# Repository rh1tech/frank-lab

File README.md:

# FRANK Lab

Official page: **[frank.rh1.tech](https://frank.rh1.tech/)** — hub for all FRANK boards and firmware.

Experimental and work-in-progress boards for the [FRANK](https://github.com/rh1tech/frank) hardware emulation platform.

**WARNING: These boards are untested and unreleased. Do NOT order PCBs from this repository.** They may contain errors, incomplete routing, or unverified component footprints. Use at your own risk.

For production-ready boards, see the main [frank](https://github.com/rh1tech/frank) repository.

## Boards in this repository

| Board | Status |
|-------|--------|
| `frank_air` | Work in progress |
| `frank_core2` | Work in progress — pulled back from the released set |
| `frank_pga` | Work in progress — single PGA2350, megafrank M2 pinout, composite + PS/2, 2-layer, hand-solderable |
| `frank_pga2` | 1.00 ready for fab, untested — dual PGA2350 (Core2 link), 2-layer, hand-solderable |
| `dino_z80` | Work in progress — pulled back from the released set |
| `xt8086_beta` | Work in progress — pulled back from the released set |
| `frank_next_proto` | Prototype — superseded by FRANK Next, released |

## Released from this repository

These boards have graduated to [rh1tech/frank](https://github.com/rh1tech/frank) and are no
longer maintained here:

| Was | Now |
|-----|-----|
| `frank_next` | [`hardware/frank_next`](https://github.com/rh1tech/frank/tree/master/hardware/frank_next) — the flagship |
| `frank_core2_proto` | [`hardware/frank_core2_proto`](https://github.com/rh1tech/frank/tree/master/hardware/frank_core2_proto) — published as a prototype |
| `frank_core2u` | [`hardware/frank_core2u`](https://github.com/rh1tech/frank/tree/master/hardware/frank_core2u) |
| `oldskoolfrank` | [`hardware/oldskool`](https://github.com/rh1tech/frank/tree/master/hardware/oldskool) |

Each carries its KiCad project, gerbers, fabrication docs, 3D-printable case and an assembly
guide in English and Russian. Board pages with full specifications are on
[frank.rh1.tech](https://frank.rh1.tech/hardware).

## Author

Mikhail Matveev — <xtreme@rh1.tech> — [rh1.tech](https://rh1.tech)

## License

© 2026 Mikhail Matveev, <xtreme@rh1.tech>

GPL v3. See [LICENSE](./LICENSE).

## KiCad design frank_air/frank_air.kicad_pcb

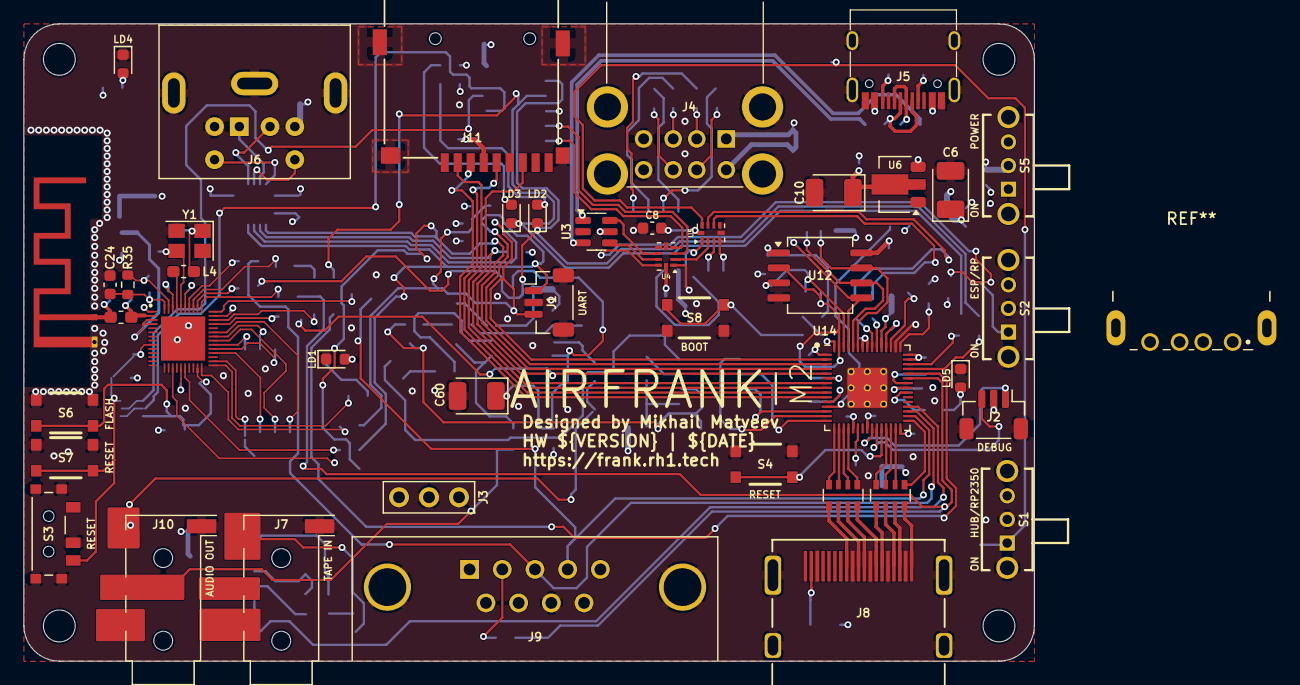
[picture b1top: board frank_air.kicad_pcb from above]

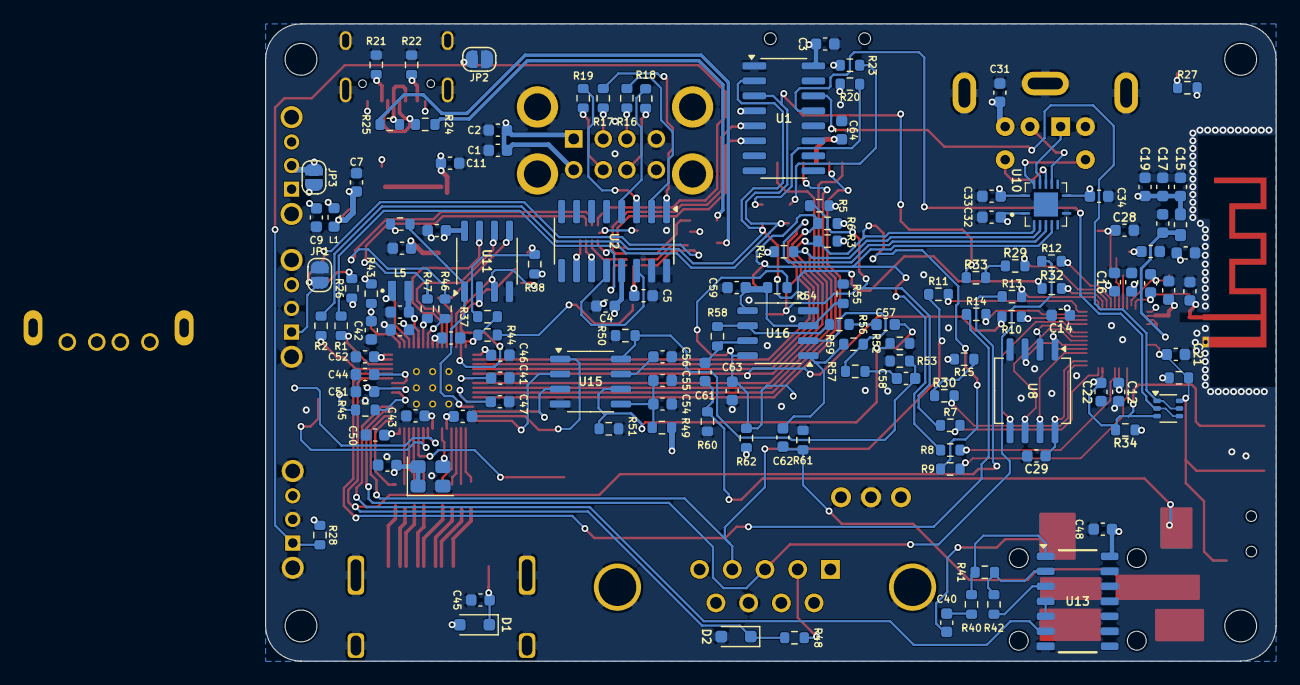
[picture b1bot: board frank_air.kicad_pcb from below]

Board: 4 copper layers, 85.6 x 54.0 mm, 183 parts (136 on the bottom side), 150 nets.

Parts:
AE1: Antenna_Shield; Antenna_2.4GHz
C1, C2, C54, C56, C57, C58, C59, C61, C62: 10u; C_0603_1608Metric
C3, C5, C7, C8, C9, C11, C31, C32, C33, C34, C35, C36, C37, C40, C41, C44, C45, C46, C47, C48, C49, C50, C51, C52, C53, C55, C63, C64: 100n; C_0603_1608Metric
C4, C38, C39, C42, C43: 4.7u; C_0603_1608Metric
C6, C10: 22u; CP_Tantalum_3528-12
C12, C19: 1u; C_0603_1608Metric_HandSolder
C13, C15, C16, C18, C20, C29: 100n; C_0603_1608Metric_HandSolder
C14: 100p; C_0603_1608Metric_HandSolder
C17: 10u; C_0603_1608Metric_HandSolder
C21, C22: 1n; C_0603_1608Metric_HandSolder
C23: 1.5pF; C_0603_1608Metric_HandSolder
C24: 10n; C_0603_1608Metric_HandSolder
C25: 2.4pF; C_0603_1608Metric_HandSolder
C26: 3.3n; C_0603_1608Metric_HandSolder
C27, C28: 12p; C_0603_1608Metric_HandSolder
C60: 10u; CP_Tantalum_3528-12
D1: 1N5819WS; D_SOD-323
D2: 3V3; D_SOD-323
H1, H2, H3, H4: Hole 2.7mm; MountingHole_2.7mm
J1: UART; JST_SH_1x03_P1.00mm_Vertical
J2: DEBUG; JST_SH_1x03_P1.00mm_Vertical
J3: PWR; PinHeader_1x03_P2.54mm
J4: SS-52100-004; USB_A_Stacked
J5: USB4215-03-A; USB_C_Receptacle
J6: MDC-036; MiniDIN_6pin_Female
J7: PJ-320D; AudioJack_3.5mm_PJ320D_TapeIn
J8: HDMI-001 19PCBTP; HDMI_Female
J9: GP2; DSUB-9_Male_TopMount
J10: PJ-320D; AudioJack_3.5mm_PJ320D_AudioOut
J11: 104031-0811; MicroSD_SMD_Long
JP1: SW1 Dbg; SolderJumper-2_P1.3mm_Open_RoundedPad1.0x1.5mm
JP2: SW2 Dbg; SolderJumper-2_P1.3mm_Open_RoundedPad1.0x1.5mm
JP3: VBUS_IN Dbg; SolderJumper-2_P1.3mm_Open_RoundedPad1.0x1.5mm
L1: 330R; L_0603_1608Metric
L2: 2nH; Inductor_0603_1608Metric_HandSolder
L3: 2.7nH/0R; Inductor_0603_1608Metric_HandSolder
L4: 24nH/0R; Inductor_0603_1608Metric_HandSolder
L5: 3.3u; L_pol_2016
LD1, LD5: Blue; LED_0603_1608Metric
LD2, LD3: Orange; LED_0603_1608Metric
LD4: Green; LED_0603_1608Metric
Q1: UMH3N; SOT-363
R1, R2, R7, R8, R9, R10, R11, R12, R13, R14, R27, R44, R45, R48: 1K; R_0603_1608Metric
R3, R4, R5, R6, R26, R28, R38, R39, R52, R53, R54, R55, R56, R57: 10K; R_0603_1608Metric
R15, R50, R51: 470R; R_0603_1608Metric
R16, R17, R18, R19, R24, R25: 22R; R_0603_1608Metric
R20, R23: 1.5K; R_0603_1608Metric
R21, R22: 5.1K; R_0603_1608Metric
R29: 499R; R_0603_1608Metric_HandSolder
R30: 0R; R_0603_1608Metric_HandSolder
R31, R34: 10K; R_0603_1608Metric_HandSolder
R32, R33: 330R; R_0603_1608Metric_HandSolder
R35: 20K; R_0603_1608Metric_HandSolder
R37: 0R; R_0603_1608Metric
R40: 4.7K; R_0603_1608Metric
R41, R42: 100K; R_0603_1608Metric
R43: 33R; R_0603_1608Metric
R46, R47: 27R; R_0603_1608Metric
R49, R62: 100R; R_0603_1608Metric
R58, R59: 47K; R_0603_1608Metric
R60, R61: 20K; R_0603_1608Metric
RN1, RN2: 270R; R_Array_4x0603
S1, S2: SK12D07VG3NS
S3: MSK12C02; Switch_Slide_MSK12C02
S4, S8: RP Reset; KMR_2
S5: SK12D07VG3NS; SK12D07VG3NS_PWR
S6: ESP Flash; KMR_2
S7: ESP Boot; KMR_2
U1: CH340C; SOP-16
U2: MW7211A; SOP-16
U3: USBLC6-2SC6; SOT-23-6
U4, U5: TS3USB221RSER; UQFN-10
U6: AMS1117-3.3; SOT-89-3
U7: ESP32-D0WD-V3; QFN35P500X500X90-49N-D
U8: W25Q32JVSIQ; SOIC-8
U10: TXS0104ERGYR; RGY_S-PVQFN-N14
U11: ESP-PSRAM32; SO-8
U12: W25Q128JVS; SOIC-8
U13: CD4069UBM; SOIC127P600X175-14N
U14: RP2350; QFN-60_RP2350A
U15: TDA1387T; SO-8
U16: LM358; SO-8
Y1: 40MHz; Crystal_SMD_3225-4Pin_3.2x2.5mm
Y2: ASE-12MHz; Oscillator_SMD_4Pin_3.2x2.5mm

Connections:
+1V1: C39.1, C41.1, C43.1, C44.1, L5.1, U14.6 (DVDD), U14.23 (DVDD), U14.39 (DVDD), U14.50 (VREG_FB)
+3.3VP: C13.1, L2.2, U7.3 (VDD3P3_1), U7.4 (VDD3P3_2)
+3V3: C3.1, C5.2, C8.2, C10.1, C11.2, C12.1, C14.1, C15.1, C16.1, C17.1, C18.1, C19.1, C20.1, C32.1, C34.1, C35.1, C36.1, C37.1, C38.1, C46.1, C47.1, C48.1, C49.1, C50.1, C51.1, C52.1, C53.1, C64.2, J3.1, J11.4 (VDD), L2.1, R3.2, R4.2, R5.2, R6.2, R20.2, R23.1, R26.1, R27.2, R28.1, R31.2, R34.2, R38.1, R39.2, R43.1, U1.4 (3V), U1.16 (VCC), U4.10 (VCC), U5.10 (VCC), U6.2 (VO), U7.1 (VDDA_1), U7.19 (VDD3P3_RTC), U7.37 (VDD3P3_CPU), U7.43 (VDDA_2), U7.46 (VDDA_3), U10.1 (VCCA), U10.8 (OE), U11.8 (VCC), U12.8 (VCC), U13.14 (VDD), U14.1 (IOVDD), U14.11 (IOVDD), U14.20 (IOVDD), U14.30 (IOVDD), U14.38 (IOVDD), U14.44 (ADC_AVDD), U14.45 (IOVDD), U14.49 (VREG_VIN), U14.53 (USB_OTP_VDD), U14.54 (QSPI_IOVDD), Y2.1 (EN), Y2.4 (Vdd)
/Audio/AMP_OUTL: C61.2, J10.T, R60.2
/Audio/AMP_OUTR: C62.2, J10.R, R61.2
/Audio/TDA_L: C57.1, R51.2, R52.1, U15.6 (A_LEFT)
/Audio/TDA_R: C58.1, R50.1, R53.1, U15.8 (A_RIGHT)
/D+: R46.1, U5.8 (D+)
/D-: R47.1, U5.7 (D-)
/ESP32/ANT: AE1.1 (A), C25.1, L3.1
/ESP32/CAP1: C24.1, C26.1, R35.2, U7.48 (CAP1)
/ESP32/CAP2: C26.2, R35.1, U7.47 (CAP2)
/ESP32/DTR: Q1.2 (B1), Q1.4 (E2), U1.13 (DTR)
/ESP32/GPIO4: R7.2, U7.24 (GPIO4)
/ESP32/GPIO13: R8.2, U7.20 (MTCK)
/ESP32/GPIO14: R9.2, U7.17 (MTMS)
/ESP32/GPIO16: R15.1, R30.2
/ESP32/GPIO18: R10.2, U7.35 (GPIO18)
/ESP32/GPIO19: R11.2, U7.38 (GPIO19)
/ESP32/GPIO21: R12.2, U7.42 (GPIO21)
/ESP32/GPIO22: R13.2, U7.39 (GPIO22)
/ESP32/GPIO23: R14.2, U7.36 (GPIO23)
/ESP32/LNA_IN: C23.1, L3.2, U7.2 (LNA_IN)
/ESP32/RTS: Q1.1 (E1), Q1.5 (B2), U1.14 (RTS)
/ESP32/SCK/CLK: U7.31 (SD_CLK), U8.6 (CLK)
/ESP32/SCS/CMD: U7.30 (SD_CMD), U8.1 (~CS)
/ESP32/SDI/SD1: U7.33 (SD_DATA_1), U8.5 (DI(IO0))
/ESP32/SDO/SD0: U7.32 (SD_DATA_0), U8.2 (DO(IO1))
/ESP32/SHD/SD2: U7.28 (SD_DATA_2), U8.7 (IO3)
/ESP32/SWP/SD3: U7.29 (SD_DATA_3), U8.3 (IO2)
/ESP32/U0RXD: R32.2, U7.40 (U0RXD)
/ESP32/U0TXD: R29.2, R33.2
/ESP32/VDD_SDIO: C29.1, U7.26 (VDD_SDIO), U8.8 (VCC)
/ESP32/XTAL_N: C27.1, U7.44 (XTAL_N), Y1.3
/ESP32/XTAL_P: L4.1, U7.45 (XTAL_P)
/ESP Buttons/ESP_FLASH: C22.1, Q1.3 (C2), R34.1, S6.2, S6.4, U7.23 (GPIO0)
/ESP Buttons/ESP_RESET: C21.1, Q1.6 (C1), R31.1, S3.3, S7.2, S7.4, U7.9 (CHIP_PU)
/GPIO0: J1.1, R5.1, R7.1, U10.4 (A3), U14.2 (GPIO0)
/GPIO1: J1.3, R6.1, R8.1, U10.5 (A4), U14.3 (GPIO1)
/GPIO2: R3.1, R9.1, U10.2 (A1), U14.4 (GPIO2)
/GPIO3: R4.1, R10.1, U10.3 (A2), U14.5 (GPIO3)
/GPIO4: J11.7 (DAT0), U14.7 (GPIO4)
/GPIO5: J11.2 (DAT3/CD), U14.8 (GPIO5)
/GPIO6: J11.5 (CLK), U14.9 (GPIO6)
/GPIO7: J11.3 (CMD), U14.10 (GPIO7)
/GPIO9: U14.13 (GPIO9), U15.3 (DATA)
/GPIO10: U14.14 (GPIO10), U15.1 (SCLK)
/GPIO11: U14.15 (GPIO11), U15.2 (LRCK)
/GPIO12: RN1.4 (R4.1), U14.16 (GPIO12)
/GPIO13: RN1.3 (R3.1), U14.17 (GPIO13)
/GPIO14: RN1.2 (R2.1), U14.18 (GPIO14)
/GPIO15: RN1.1 (R1.1), U14.19 (GPIO15)
/GPIO16: RN2.4 (R4.1), U14.27 (GPIO16)
/GPIO17: RN2.3 (R3.1), U14.28 (GPIO17)
/GPIO18: RN2.2 (R2.1), U14.29 (GPIO18)
/GPIO19: RN2.1 (R1.1), U14.31 (GPIO19)
/GPIO20: J9.4, R11.1, U14.32 (GPIO20)
/GPIO21: J9.3, R12.1, U14.33 (GPIO21)
/GPIO22: U13.6 (I=*C), U14.34 (GPIO22)
/GPIO26: D2.1 (K), R13.1, R48.1, U14.40 (GPIO26_ADC0)
/GPIO27: R14.1, U14.41 (GPIO27_ADC1)
/GPIO28: LD2.1 (K), R2.1, R32.1, U1.2 (TxD)
/GPIO29: LD3.1 (K), R1.1, R33.1, U1.3 (RxD)
/PS2/KB_CLK_5V: J6.5, U10.13 (B1)
/PS2/KB_DATA_5V: J6.1, U10.12 (B2)
/PS2/MS_CLK_5V: J6.6, U10.11 (B3)
/PS2/MS_DATA_5V: J6.2, U10.10 (B4)
/Power/SW1: JP1.2 (B), R26.2, S2.1, U4.9 (S)
/Power/SW2: JP2.2 (B), R28.2, S1.1, U5.9 (S)
/Power/TC_D+: U3.4 (I/O2), U4.8 (D+)
/Power/TC_D-: U3.6 (I/O1), U4.7 (D-)
/Power/UH_D+: U2.11 (DPU), U5.3 (2D+)
/Power/UH_D-: U2.10 (DMU), U5.4 (2D-)
/Power/US_D1+: R16.1, U2.2 (DP0)
/Power/US_D1-: R17.1, U2.1 (DM0)
/Power/US_D2+: R18.1, U2.4 (DP1)
/Power/US_D2-: R19.1, U2.3 (DM1)
/Power/UT_D+: U1.5 (D+), U4.3 (2D+)
/Power/UT_D-: U1.6 (D-), U4.4 (2D-)
/Power/VBUS_IN: J5.2 (VBUS), J5.11 (VBUS), JP3.1 (A), S5.2
/RP2350A/FLASH_SS: R37.2, R38.2, U12.1 (~CS)
/RP2350A/GPIO8: R39.1, U11.1 (~CE), U14.12 (GPIO8)
/RP2350A/GPIO28: R2.2, U14.42 (GPIO28_ADC2)
/RP2350A/GPIO29: R1.2, U14.43 (GPIO29_ADC3)
/RP2350A/QSPI_SCLK: U11.6 (SCLK), U12.6 (CLK), U14.56 (QSPI_SCLK)
/RP2350A/QSPI_SD0: U11.5 (SI/SIO), U12.5 (DI(IO0)), U14.57 (QSPI_SD0)
/RP2350A/QSPI_SD1: U11.2 (SO/SIO), U12.2 (DO(IO1)), U14.59 (QSPI_SD1)
/RP2350A/QSPI_SD2: U11.3 (SIO2), U12.3 (IO2), U14.58 (QSPI_SD2)
/RP2350A/QSPI_SD3: U11.7 (SIO3), U12.7 (IO3), U14.55 (QSPI_SD3)
/RP2350A/QSPI_SS: R37.1, R44.1, U14.60 (QSPI_SS)
/RP2350A/SWCLK: J2.3, U14.24 (SWCLK)
/RP2350A/SWD: J2.1, U14.25 (SWD)
/RP2350A/VREG_AVDD: C42.1, R43.2, U14.46 (VREG_AVDD)
/RP2350A/VREG_LX: L5.2, U14.48 (VREG_LX)
/RP2350A/XIN: U14.21 (XIN), Y2.3 (OUT)
/RP2350A/~USB_BOOT: R44.2, S8.2, S8.4
/RUN: S4.2, S4.4, U14.26 (RUN)
/Tape In/TAPE: C40.2, J7.T
GND: AE1.2 (Shield), C1.2, C2.2, C3.2, C4.2, C5.1, C6.2, C7.1, C8.1, C9.2, C10.2, C11.1, C12.2, C13.2, C14.2, C15.2, C16.2, C17.2, C18.2, C19.2, C20.2, C21.2, C22.2, C23.2, C24.2, C25.2, C27.2, C28.2, C29.2, C31.2, C32.2, C33.2, C34.2, C35.2, C36.2, C37.2, C38.2, C39.2, C41.2, C42.2, C43.2, C44.2, C45.2, C46.2, C47.2, C48.2, C49.2, C50.2, C51.2, C52.2, C53.2, C54.2, C55.2, C56.2, C59.1, C60.2, C63.1, C64.1, D2.2 (A), J1.2, J2.2, J3.2, J4.4 (GND1), J4.8 (GND2), J4.SH (Shield), J5.1 (GND), J5.12 (GND), J5.13 (SHIELD), J6.3, J7.S, J8.2 (G_D2), J8.5 (G_D1), J8.8 (G_D0), J8.11 (G_CLK), J8.17 (G_DDC/CEC), J8.20 (SHIELD1), J8.21 (SHIELD2), J8.22 (SHIELD3), J8.23 (SHIELD4), J9.8, J10.S, J11.6 (VSS), J11.SH (SHIELD), JP1.1 (A), JP2.1 (A), LD1.1 (K), LD4.1 (K), LD5.1 (K), R21.1, R22.1, R50.2, R51.1, R52.2, R53.2, R55.1, R60.1, R61.1, S1.2, S2.2, S3.2, S4.1, S4.3, S6.1, S6.3, S7.1, S7.3, S8.1, S8.3, U1.1 (GND), U2.15 (GND), U2.16 (GND), U3.2 (GND), U4.5 (GND), U4.6 (~OE), U5.5 (GND), U5.6 (~OE), U6.1 (GND), U7.49 (GND), U8.4 (GND), U10.7 (GND), U10.15 (THERMAL_PAD), U11.4 (VSS), U12.4 (GND), U13.7 (VSS), U13.9 (D14), U13.11 (E), U13.13 (F), U14.47 (VREG_PGND), U14.61 (GND), U15.4 (AGND), U16.4 (V-), Y1.2, Y1.4, Y2.2 (GND)
GPIO25: R45.2, U14.37 (GPIO25)
unnamed: C28.1, L4.2, Y1.1
unnamed: C40.1, R40.2
unnamed: C57.2, R56.2
unnamed: C58.2, R57.2
unnamed: C61.1, R58.1, U16.7
unnamed: C62.1, R59.1, U16.1
unnamed: C45.1, D1.1 (K), J8.18 (+5V)
unnamed: J4.3 (D1+), R16.2
unnamed: J4.2 (D1-), R17.2
unnamed: J4.7 (D2+), R18.2
unnamed: J4.6 (D2-), R19.2
unnamed: J5.4 (CC1), R21.2
unnamed: J5.10 (CC2), R22.2
unnamed: J5.5 (DN2), J5.7 (DN1), R24.2
unnamed: J5.6 (DP1), J5.8 (DP2), R25.2
unnamed: J8.12 (CLKN), RN1.5 (R4.2)
unnamed: J8.10 (CLKP), RN1.6 (R3.2)
unnamed: J8.9 (D0N), RN1.7 (R2.2)
unnamed: J8.7 (D0P), RN1.8 (R1.2)
unnamed: J8.6 (D1N), RN2.5 (R4.2)
unnamed: J8.4 (D1P), RN2.6 (R3.2)
unnamed: J8.3 (D2N), RN2.7 (R2.2)
unnamed: J8.1 (D2P), RN2.8 (R1.2)
unnamed: J9.2, R48.2
unnamed: C9.1, JP3.2 (B), L1.2, S5.1
unnamed: LD1.2 (A), R15.2
unnamed: LD2.2 (A), R20.1
unnamed: LD3.2 (A), R23.2
unnamed: LD4.2 (A), R27.1
unnamed: LD5.2 (A), R45.1
unnamed: R24.1, U3.1 (I/O1)
unnamed: R25.1, U3.3 (I/O2)
unnamed: U2.12 (VD33), U2.14 (VD3)
unnamed: U4.1 (1D+), U5.1 (1D+)
unnamed: U4.2 (1D-), U5.2 (1D-)
unnamed: R30.1, U7.25 (GPIO16)
unnamed: R29.1, U7.41 (U0TXD)
unnamed: R40.1, R41.2, U13.1 (A)
unnamed: R42.1, U13.3 (B)
unnamed: U13.4 (H=*B), U13.5 (C)
unnamed: R41.1, R42.2, U13.2 (G-*A)
unnamed: R47.2, U14.51 (USB_DM)
unnamed: R46.2, U14.52 (USB_DP)
unnamed: C56.1, U15.7 (FLT)
unnamed: C54.1, C55.1, R49.1, U15.5 (VA)
unnamed: C59.2, R54.1, R55.2, U16.3 (+), U16.5 (+)
unnamed: R57.1, R59.2, U16.2 (-)
unnamed: R56.1, R58.2, U16.6 (-)
unnamed: C60.1, C63.2, R54.2, R62.2, U16.8 (V+)
VBUS: C1.1, C2.1, C4.1, C6.1, C7.2, C31.1, C33.1, D1.2 (A), J3.3, J4.1 (VBUS1), J4.5 (VBUS2), J6.4, J9.6, L1.1, R49.2, R62.1, U2.13 (VDD5), U3.5 (VBUS), U6.3 (VI), U10.14 (VCCB)

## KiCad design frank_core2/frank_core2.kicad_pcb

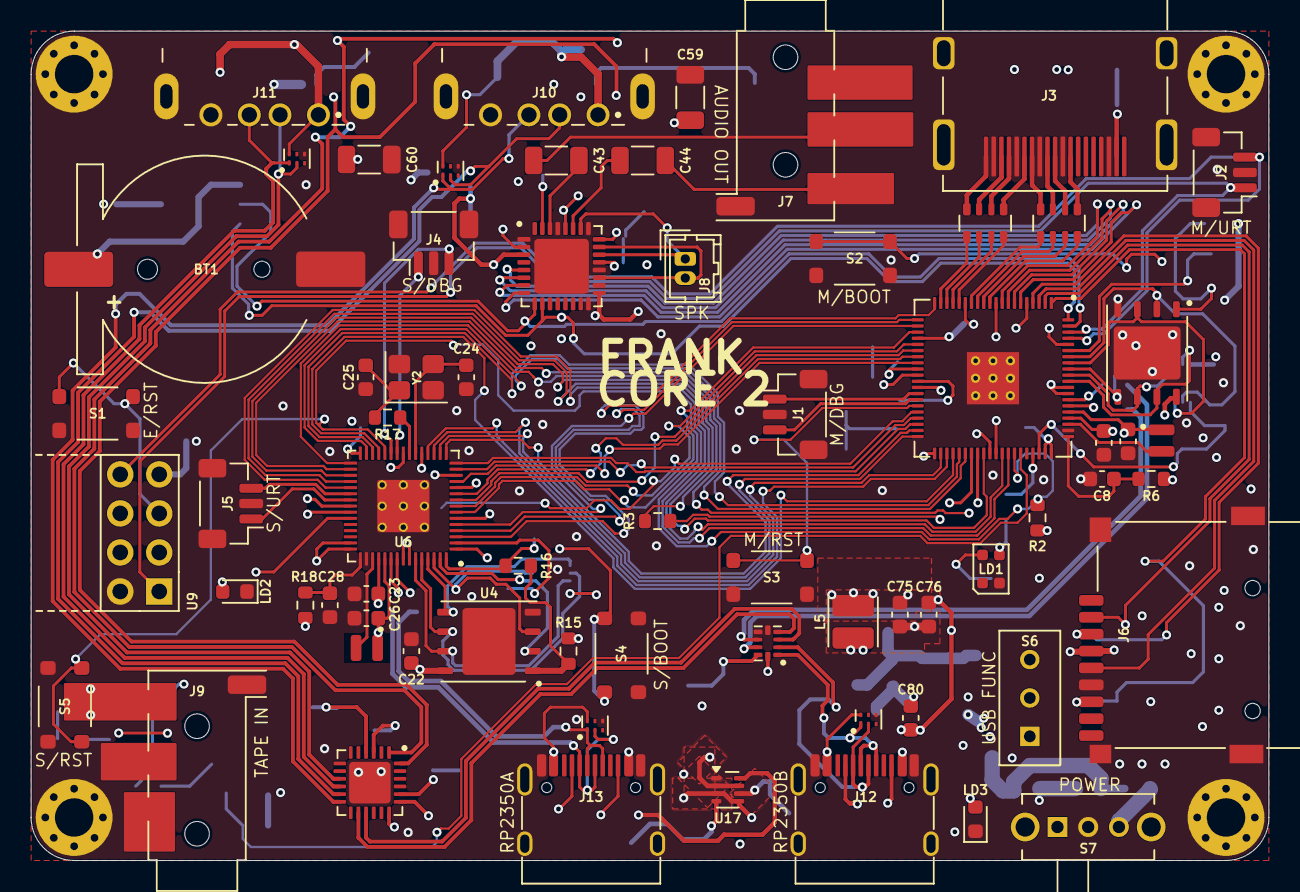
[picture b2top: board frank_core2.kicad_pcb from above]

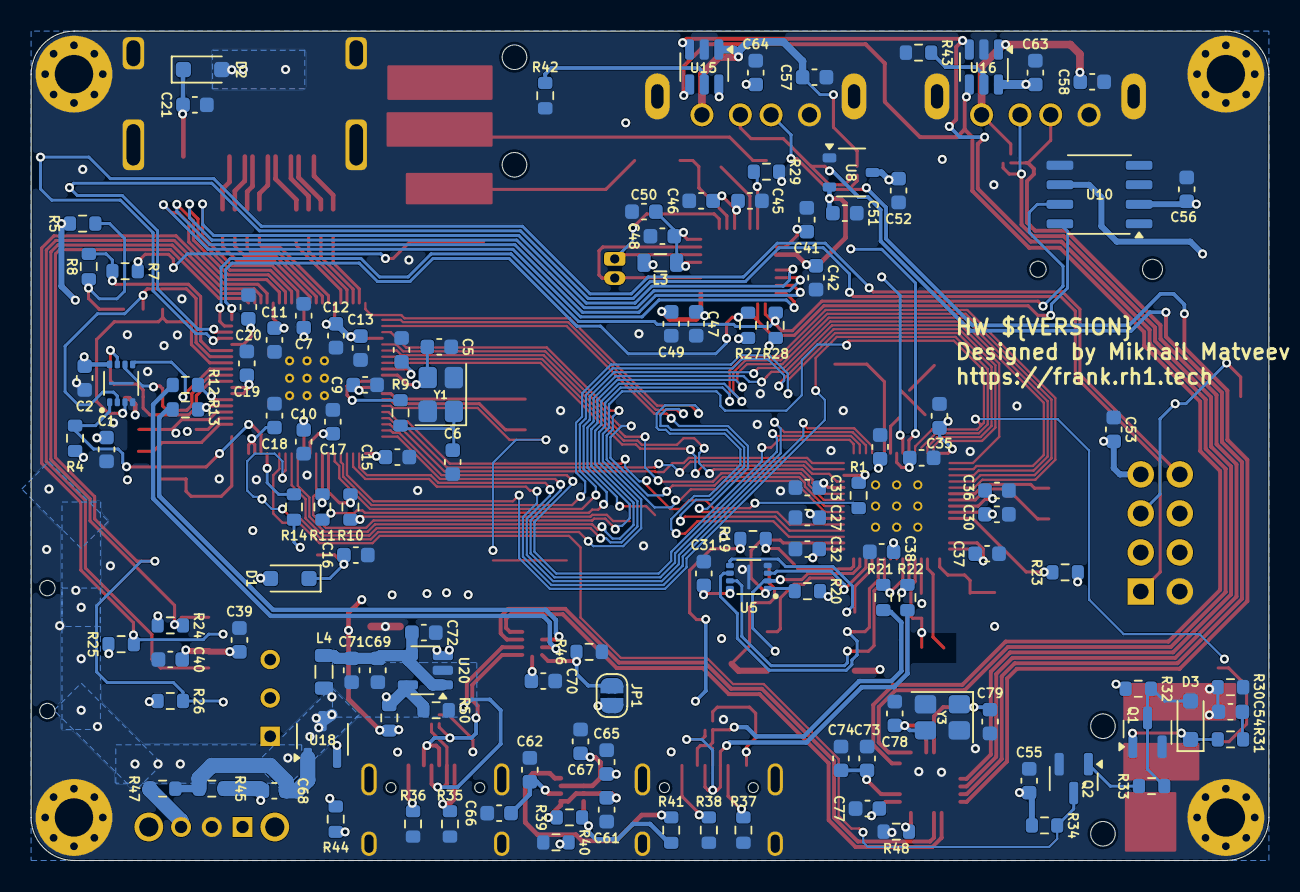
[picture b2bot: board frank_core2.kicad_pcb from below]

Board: 4 copper layers, 80.6 x 54.0 mm, 195 parts (125 on the bottom side), 161 nets.

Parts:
BT1: CR1220; Battery_CR1220
C1, C2, C7, C10, C11, C12, C13, C14, C15, C16, C17, C18, C19, C20, C21, C22, C27, C30, C31, C32, C33, C34, C35, C36, C37, C38, C40, C41, C42, C46, C49, C50, C53, C54, C55, C56, C57, C58, C61, C62, C68, C70, C72: 100nF; C_0603_1608Metric
C3, C4, C8, C9, C23, C26, C28, C29: 4.7uF; C_0603_1608Metric
C5, C6, C24, C25: 15pF; C_0603_1608Metric
C39, C45, C47, C48, C63, C64, C65, C66, C67, C69, C71, C73, C75, C76, C77: 10uF; C_0603_1608Metric
C43, C44, C59, C60: 100uF; C_1206_3216Metric
C51, C52, C74: 1uF; C_0603_1608Metric
C78, C79: 12pF; C_0603_1608Metric
C80: 22pF; C_0603_1608Metric
D1, D2: 1N5819WS; D_SOD-323
D3: 1N4148; D_SOD-323
H1, H2, H3, H4: MountingHole; MountingHole_2.5mm_Pad_Via
J1, J4: Debug; JST_SH_1x03_P1.00mm_Vertical
J2, J5: UART; JST_SH_1x03_P1.00mm_Vertical
J3: HDMI-001 19PCBTP; HDMI_Female
J6: 104031-0811; MicroSD_SMD_Long
J7: PJ-320D; AudioJack_3.5mm_PJ320D_AudioOut
J8: Speaker; JST_GH_1x02_P1.25mm
J9: PJ-320D; AudioJack_3.5mm_PJ320D_TapeIn
J10, J11: AF 10.0 HC6.3; USB_A_Short
J12, J13: USB4215-03-A; USB_C_Receptacle
JP1: USB Debug; SolderJumper-2_P1.3mm_Open_RoundedPad1.0x1.5mm
L1, L2: 3.3µH; L_AOTA-B201610_2.0x1.6mm
L3, L4: 330R 2A; L_0805_2012Metric
L5: 2.2uH; L_Cenker_CKCS3015
LD1: WS2812B-2020; LED_WS2812B-2020_PLCC4_2.0x2.0mm
LD2: Blue; LED_0603_1608Metric
LD3: Green; LED_0603_1608Metric
Q1, Q2: BC850; SOT-23
R1, R3, R6, R18: 33R; R_0603_1608Metric
R2, R4, R5, R15, R20, R24, R25, R26, R29, R31, R32, R33, R46: 10K; R_0603_1608Metric
R7, R9, R10, R11, R17, R19, R23, R34, R44, R47: 1K; R_0603_1608Metric
R8, R16: 0R; R_0603_1608Metric
R12, R13, R21, R22: 27R; R_0603_1608Metric
R14: 330R; R_0603_1608Metric
R27, R28, R48: 4.7K; R_0603_1608Metric
R30: 100R; R_0603_1608Metric
R35, R36, R37, R38: 5.1K; R_0603_1608Metric
R39: 300K; R_0603_1608Metric
R40, R42, R43, R45, R49: 100K; R_0603_1608Metric
R41: 1M; R_0603_1608Metric
R50: 22K; R_0603_1608Metric
RN1, RN2: 270R; R_Array_4x0603
S1: ESP Reset; Button_SMD_3x4x2mm
S2, S4: RP Boot; Button_SMD_3x4x2mm
S3, S5: RP Reset; Button_SMD_3x4x2mm
S6: SS12D00; Switch_Slide_SS12D00
S7: SK12D07VG3NS; Switch_Slide_SK12D07VG3NS_PWR
U1, U5: APS6404L-3SQR-ZR; PSON50P200X300X50-9N
U2, U4: W25Q128JVPIQ; WSON-8-1EP_6x5mm_P1.27mm_EP3.45x4.35mm
U3: RP2350B; RP2350-QFN-80_10x10_P0.4mm
U6: RP2350; QFN-60-1EP_7x7mm_P0.4mm_EP3.4x3.4mm
U7: TLV320DAC3100IRHBR
U8: XC6206P182MR-G
U9: ESP-01v090; ESP-01
U10: DS3231MZ; SO-8_3.9x4.9mm_P1.27mm
U11, U12, U13, U14: TPD4S012DRYR
U15, U16: CH217K; SOT-23-6
U17: TPS2116DRL; SOT-583-8
U18: AO3401A; SOT-23-3L_AOS
U19: TS3USB221RSER; UQFN-10
U20: SY8089AAAC; SOT-23-5
U21: CH334F; QFN-24-1EP_4x4mm_P0.5mm_EP2.7x2.7mm
Y1, Y2, Y3: 12 MHz; Crystal_SMD_3225-4Pin_3.2x2.5mm

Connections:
+1V1: C4.1, C7.1, C9.1, C10.1, L1.1, U3.10 (DVDD), U3.32 (DVDD), U3.51 (DVDD), U3.65 (VREG_FB)
+1V1_A: C26.1, C27.1, C29.1, C30.1, L2.1, U6.6 (DVDD), U6.23 (DVDD), U6.39 (DVDD), U6.50 (VREG_FB)
+1V8: C42.2, C51.2, U7.3 (DVDD), U8.2 (VOUT)
+3V3: C1.1, C2.2, C3.1, C11.1, C12.1, C13.1, C14.1, C15.1, C17.1, C18.1, C19.1, C20.1, C22.1, C23.1, C31.2, C32.1, C33.1, C34.1, C35.1, C36.1, C37.1, C38.1, C39.2, C40.2, C41.1, C45.2, C46.2, C47.2, C49.2, C52.2, C53.1, C55.2, C56.1, C70.2, C75.1, C76.1, C80.1, J6.4 (VDD), JP1.1 (A), L5.1, R2.2, R4.2, R5.2, R6.1, R15.2, R18.1, R20.2, R24.1, R25.1, R26.1, R27.2, R28.2, R29.2, R32.1, R34.1, R44.2, R49.1, S6.2, U1.8 (VDD), U2.8 (VCC), U3.5 (IOVDD), U3.15 (IOVDD), U3.24 (IOVDD), U3.29 (IOVDD), U3.41 (IOVDD), U3.50 (IOVDD), U3.59 (ADC_AVDD), U3.60 (IOVDD), U3.64 (VREG_VIN), U3.68 (USB_OTP_VDD), U3.69 (QSPI_IOVDD), U3.76 (IOVDD), U4.8 (VCC), U5.8 (VDD), U6.1 (IOVDD), U6.11 (IOVDD), U6.20 (IOVDD), U6.30 (IOVDD), U6.38 (IOVDD), U6.44 (ADC_AVDD), U6.45 (IOVDD), U6.49 (VREG_VIN), U6.53 (USB_OTP_VDD), U6.54 (QSPI_IOVDD), U7.2 (IOVDD), U7.17 (AVDD), U7.28 (HPVDD), U8.3 (VIN), U9.7 (VCC), U10.2 (VCC), U19.10 (VCC)
/Audio/+5V_SPK: C48.2, C50.2, L3.1, U7.21 (SPKVDD_1), U7.24 (SPKVDD_2)
/Audio/SPKM: J8.2, U7.19 (SPKM_1), U7.23 (SPKM_2)
/Audio/SPKP: J8.1, U7.22 (SPKP_1), U7.26 (SPKP_2)
/ESP01/ERST: S1.1, S1.3, U9.5 (RST)
/ESP01/RX: J2.1, U3.77 (GPIO0), U9.8 (URXD)
/ESP01/TX: J2.3, U3.78 (GPIO1), U9.1 (UTXD)
/GPIO2/SDA: R28.1, U3.79 (GPIO2), U7.9 (SDA), U10.7 (SDA)
/GPIO3/SCL: R27.1, U3.80 (GPIO3), U7.10 (SCL), U10.8 (SCL)
/GPIO8/MCLK: U3.6 (GPIO8), U7.8 (MCLK)
/GPIO9/BCLK: U3.7 (GPIO9), U7.7 (BCLK)
/GPIO10/WCLK: U3.8 (GPIO10), U7.6 (WCLK)
/GPIO11/DIN: U3.9 (GPIO11), U7.5 (DIN)
/GPIO12/CLKN: RN1.4 (R4.1), U3.11 (GPIO12)
/GPIO13/CLKP: RN1.3 (R3.1), U3.12 (GPIO13)
/GPIO14/D0N: RN1.2 (R2.1), U3.13 (GPIO14)
/GPIO15/D0P: RN1.1 (R1.1), U3.14 (GPIO15)
/GPIO16/D1N: RN2.4 (R4.1), U3.16 (GPIO16)
/GPIO17/D1P: RN2.3 (R3.1), U3.17 (GPIO17)
/GPIO18/D2N: RN2.2 (R2.1), U3.18 (GPIO18)
/GPIO19/D2P: RN2.1 (R1.1), U3.19 (GPIO19)
/RP2350A/BOOT: R19.2, S4.1, S4.3
/RP2350A/D+: J13.6 (DP1), J13.8 (DP2), R21.1, U14.1 (D+)
/RP2350A/D-: J13.5 (DN2), J13.7 (DN1), R22.1, U14.2 (D-_)
/RP2350A/GPIO0: R20.1, U5.1 (~CE), U6.2 (GPIO0)
/RP2350A/GPIO9: R1.2, U6.13 (GPIO9)
/RP2350A/GPIO24/UART_1: J5.1, U6.36 (GPIO24)
/RP2350A/GPIO25/UART_3: J5.3, U6.37 (GPIO25)
/RP2350A/QSPI_SCLK: U4.6 (CLK), U5.6 (SCLK), U6.56 (QSPI_SCLK)
/RP2350A/QSPI_SD0: U4.5 (DI_(IO0)), U5.5 (SI/SIO(0)), U6.57 (QSPI_SD0)
/RP2350A/QSPI_SD1: U4.2 (DO_(IO1)), U5.2 (SO/SIO(1)), U6.59 (QSPI_SD1)
/RP2350A/QSPI_SD2: U4.3 (~WP_(IO2)), U5.3 (SIO(2)), U6.58 (QSPI_SD2)
/RP2350A/QSPI_SD3: U4.7 (~HOLD_OR_/RESET_(IO3)), U5.7 (SIO(3)), U6.55 (QSPI_SD3)
/RP2350A/QSPI_SS: R16.1, R19.1, U6.60 (QSPI_SS)
/RP2350A/SWCLK: J4.3, U6.24 (SWCLK)
/RP2350A/SWD: J4.1, U6.25 (SWD)
/RP2350A/VREG_AVDD: C28.1, R18.2, U6.46 (VREG_AVDD)
/RP2350A/VREG_LX: L2.2, U6.48 (VREG_LX)
/RP2350A/XIN: C24.1, U6.21 (XIN), Y2.3
/RP2350A/XOUT: R17.2, U6.22 (XOUT)
/RP2350B/BOOT: R7.2, S2.1, S2.3
/RP2350B/D+: R12.1, U19.8 (D+)
/RP2350B/D-: R13.1, U19.7 (D-)
/RP2350B/GPIO38: R3.1, R10.2
/RP2350B/GPIO44: Q2.3 (C), R34.2, U3.55 (GPIO44_ADC4)
/RP2350B/GPIO47: R4.1, U1.1 (~CE), U3.58 (GPIO47_ADC7)
/RP2350B/QSPI_SCLK: U1.6 (SCLK), U2.6 (CLK), U3.71 (QSPI_SCLK)
/RP2350B/QSPI_SD0: U1.5 (SI/SIO(0)), U2.5 (DI_(IO0)), U3.72 (QSPI_SD0)
/RP2350B/QSPI_SD1: U1.2 (SO/SIO(1)), U2.2 (DO_(IO1)), U3.74 (QSPI_SD1)
/RP2350B/QSPI_SD2: U1.3 (SIO(2)), U2.3 (~WP_(IO2)), U3.73 (QSPI_SD2)
/RP2350B/QSPI_SD3: U1.7 (SIO(3)), U2.7 (~HOLD_OR_/RESET_(IO3)), U3.70 (QSPI_SD3)
/RP2350B/QSPI_SS: R7.1, R8.1, U3.75 (QSPI_SS)
/RP2350B/RUN: S3.1, S3.3, U3.35 (RUN)
/RP2350B/SWCLK: J1.3, U3.33 (SWCLK)
/RP2350B/SWD: J1.1, U3.34 (SWD)
/RP2350B/VREG_AVDD: C8.1, R6.2, U3.61 (VREG_AVDD)
/RP2350B/VREG_LX: L1.2, U3.63 (VREG_LX)
/RP2350B/XIN: C5.1, U3.30 (XIN), Y1.3
/RP2350B/XOUT: R9.2, U3.31 (XOUT)
/RP2350/20B/1A/D0: U3.20 (GPIO20), U6.3 (GPIO1)
/RP2350/21B/2A/D1: U3.21 (GPIO21), U6.4 (GPIO2)
/RP2350/22B/3A/D2: U3.22 (GPIO22), U6.5 (GPIO3)
/RP2350/23B/4A/D3: U3.23 (GPIO23), U6.7 (GPIO4)
/RP2350/24B/5A/D4: U3.25 (GPIO24), U6.8 (GPIO5)
/RP2350/25B/6A/D5: U3.26 (GPIO25), U6.9 (GPIO6)
/RP2350/26B/7A/D6: U3.27 (GPIO26), U6.10 (GPIO7)
/RP2350/27B/8A/D7: U3.28 (GPIO27), U6.12 (GPIO8)
/RP2350/28B/9A/CLK: R1.1, U3.36 (GPIO28)
/RP2350/29B/10A/VALID: U3.37 (GPIO29), U6.14 (GPIO10)
/RP2350/30B/11A/D0: U3.38 (GPIO30), U6.15 (GPIO11)
/RP2350/31B/12A/D1: U3.39 (GPIO31), U6.16 (GPIO12)
/RP2350/32B/13A/D2: U3.40 (GPIO32), U6.17 (GPIO13)
/RP2350/33B/14A/D3: U3.42 (GPIO33), U6.18 (GPIO14)
/RP2350/34B/15A/D4: U3.43 (GPIO34), U6.19 (GPIO15)
/RP2350/35B/16A/D5: U3.44 (GPIO35), U6.27 (GPIO16)
/RP2350/36B/17A/D6: U3.45 (GPIO36), U6.28 (GPIO17)
/RP2350/37B/18A/D7: U3.46 (GPIO37), U6.29 (GPIO18)
/RP2350/38B/19A/CLK: R3.2, U6.31 (GPIO19)
/RP2350/39B/20A/VALID: R11.2, U6.32 (GPIO20)
/RP2350/40B/21A/FS: U3.49 (GPIO40_ADC0), U6.33 (GPIO21)
/RP2350/41B/22A/DB_MS: U3.52 (GPIO41_ADC1), U6.34 (GPIO22)
/RP2350/42B/23A/DB_SM: U3.53 (GPIO42_ADC2), U6.35 (GPIO23)
/RP2350/43B/RUNA/SR: R2.1, S5.1, S5.3, U3.54 (GPIO43_ADC3), U6.26 (RUN)
/SD/CDDAT3/GPIO5: J6.2 (DAT3/CD), R24.2, U3.2 (GPIO5)
/SD/CLK/GPIO6: J6.5 (CLK), U3.3 (GPIO6)
/SD/CMD/GPIO7: J6.3 (CMD), R25.2, U3.4 (GPIO7)
/SD/DAT0/GPIO4: J6.7 (DAT0), R26.2, U3.1 (GPIO4)
/Tape/TAPE: C54.1, J9.T, R30.1
/USB/+5V_BUCK: C69.1, C71.1, C72.1, L4.2, U20.1 (EN), U20.4 (IN)
/USB/D2+: J12.6 (DP1), J12.8 (DP2), U13.1 (D+), U19.1 (1D+)
/USB/D2-: J12.5 (DN2), J12.7 (DN1), U13.2 (D-_), U19.2 (1D-)
/USB/DH+: U19.3 (2D+), U21.15 (DPU+)
/USB/DH-: U19.4 (2D-), U21.14 (DMU-)
/USB/DS1+: J10.3 (D+), U11.1 (D+), U21.12 (DP1+)
/USB/DS1-: J10.2 (D-), U11.2 (D-_), U21.11 (DM1-)
/USB/DS2+: J11.3 (D+), U12.1 (D+), U21.10 (DP2+)
/USB/DS2-: J11.2 (D-), U12.2 (D-_), U21.9 (DM2-)
/USB/OVCUR: U15.3 (FLAG#), U16.3 (FLAG#), U21.1 (~OVCUR)
/USB/PWREN: U15.4 (EN#), U16.4 (EN#), U21.24 (~PWREN)
/USB/S: JP1.2 (B), R46.2, S6.3, U19.9 (S)
/USB/ST: R41.2, U17.8 (ST)
/USB/VBUS_IN: C67.1, C68.2, R45.2, U17.2 (VOUT), U17.7 (VOUT), U18.2 (S)
/USB/VBUS_IN1: C61.2, C65.2, J13.2 (VBUS), J13.11 (VBUS), R39.2, U14.6 (VBUS), U17.3 (VIN1), U17.5 (MODE)
/USB/VBUS_IN2: C62.2, C66.2, J12.2 (VBUS), J12.11 (VBUS), U13.6 (VBUS), U17.6 (VIN2)
/USB/VBUS_P1: C57.1, C59.1, J10.1 (VBUS), U11.6 (VBUS), U15.1 (VOUT)
/USB/VBUS_P2: C58.1, C60.1, J11.1 (VBUS), U12.6 (VBUS), U16.1 (VOUT)
/USB/VDD33: C73.2, C74.2, U21.20 (VDD33_{LDO})
/USB/XTAL_N: C78.1, U21.3 (XO), Y3.3
/USB/XTAL_P: C79.1, U21.4 (XI), Y3.1
GND: BT1.2 (-), C1.2, C2.1, C3.2, C4.2, C5.2, C6.2, C7.2, C8.2, C9.2, C10.2, C11.2, C12.2, C13.2, C14.2, C15.2, C16.2, C17.2, C18.2, C19.2, C20.2, C21.2, C22.2, C23.2, C24.2, C25.2, C26.2, C27.2, C28.2, C29.2, C30.2, C31.1, C32.2, C33.2, C34.2, C35.2, C36.2, C37.2, C38.2, C39.1, C40.1, C41.2, C42.1, C45.1, C46.1, C47.1, C48.1, C49.1, C50.1, C51.1, C52.1, C53.2, C55.1, C56.2, C57.2, C58.2, C59.2, C60.2, C61.1, C62.1, C63.1, C64.1, C65.1, C66.1, C67.2, C69.2, C70.1, C71.2, C72.2, C73.1, C74.1, C75.2, C76.2, C77.1, C78.2, C79.2, H1.1 (1_1), H2.1 (1_1), H3.1 (1_1), H4.1 (1_1), J1.2, J2.2, J3.2 (G_D2), J3.5 (G_D1), J3.8 (G_D0), J3.11 (G_CLK), J3.17 (G_DDC/CEC), J3.20 (SHIELD1), J3.21 (SHIELD2), J3.22 (SHIELD3), J3.23 (SHIELD4), J4.2, J5.2, J6.6 (VSS), J6.SH (SHIELD), J7.S, J9.S, J10.4 (GND), J10.5 (Shield), J11.4 (GND), J11.5 (Shield), J12.1 (GND), J12.12 (GND), J12.13 (SHIELD), J13.1 (GND), J13.12 (GND), J13.13 (SHIELD), LD1.2 (VSS), LD2.1 (K), LD3.1 (K), Q1.2 (E), Q2.2 (E), R30.2, R35.1, R36.1, R37.1, R38.1, R40.1, R42.1, R43.1, R46.1, R48.2, R50.2, S1.2, S1.4, S2.2, S2.4, S3.2, S3.4, S4.2, S4.4, S5.2, S5.4, S7.2, U1.4 (VSS), U1.9 (EXP), U2.4 (GND_1), U2.9 (GND_2), U3.62 (VREG_PGND), U3.81 (GND), U4.4 (GND_1), U4.9 (GND_2), U5.4 (VSS), U5.9 (EXP), U6.47 (VREG_PGND), U6.61 (GND), U7.1 (IOVSS), U7.16 (AVSS), U7.18 (DVSS), U7.20 (SPKVSS_1), U7.25 (SPKVSS_2), U7.29 (HPVSS), U7.33 (EP), U8.1 (VSS), U9.2 (GND), U10.5 (GND), U11.4 (GND), U12.4 (GND), U13.4 (GND), U14.4 (GND), U15.2 (GND), U16.2 (GND), U17.1 (GND), U19.5 (GND), U19.6 (~OE), U20.2 (GND), U21.25 (GND), Y1.2, Y1.4, Y2.2, Y2.4, Y3.2, Y3.4
unnamed: BT1.1 (+), U10.6 (VBAT)
unnamed: C6.1, R9.1, Y1.1
unnamed: C25.1, R17.1, Y2.1
unnamed: C43.1, J7.R
unnamed: C44.1, J7.T
unnamed: C54.2, R31.1
unnamed: C16.1, D1.1 (K), LD1.4 (VDD)
unnamed: C21.1, D2.1 (K), J3.18 (+5V)
unnamed: D3.2 (A), Q1.3 (C), R32.2, R33.1
unnamed: D3.1 (K), Q1.1 (B), R31.2
unnamed: J3.12 (CLKN), RN1.5 (R4.2)
unnamed: J3.10 (CLKP), RN1.6 (R3.2)
unnamed: J3.9 (D0N), RN1.7 (R2.2)
unnamed: J3.7 (D0P), RN1.8 (R1.2)
unnamed: J3.6 (D1N), RN2.5 (R4.2)
unnamed: J3.4 (D1P), RN2.6 (R3.2)
unnamed: J3.3 (D2N), RN2.7 (R2.2)
unnamed: J3.1 (D2P), RN2.8 (R1.2)
unnamed: J12.4 (CC1), R35.2
unnamed: J12.10 (CC2), R36.2
unnamed: J13.4 (CC1), R37.2
unnamed: J13.10 (CC2), R38.2
unnamed: LD1.3 (DIN), R14.1
unnamed: LD2.2 (A), R23.1
unnamed: LD3.2 (A), R44.1
unnamed: Q2.1 (B), R33.2
unnamed: R47.2, S7.3
unnamed: R5.1, R8.2, U2.1 (~CS)
unnamed: R10.1, U3.47 (GPIO38)
unnamed: R11.1, U3.48 (GPIO39)
unnamed: R14.2, U3.57 (GPIO46_ADC6)
unnamed: R13.2, U3.66 (USB_DM)
unnamed: R12.2, U3.67 (USB_DP)
unnamed: R15.1, R16.2, U4.1 (~CS)
unnamed: R23.2, U6.40 (GPIO26_ADC0)
unnamed: R22.2, U6.51 (USB_DM)
unnamed: R21.2, U6.52 (USB_DP)
unnamed: C44.2, U7.27 (HPL)
unnamed: C43.2, U7.30 (HPR)
unnamed: R29.1, U7.31 (~RESET)
unnamed: R42.2, U15.5 (ISET)
unnamed: R43.2, U16.5 (ISET)
unnamed: R39.1, R40.2, R41.1, U17.4 (PR1)
unnamed: C68.1, R45.1, R47.1, U18.1 (G)
unnamed: C80.2, R49.2, R50.1, U20.5 (FB)
unnamed: L5.2, U20.3 (LX)
unnamed: R48.1, U21.18 (PSELF)
VBUS: C63.2, C64.2, C77.2, D1.2 (A), D2.2 (A), L3.2, L4.1, U15.6 (VIN), U16.6 (VIN), U18.3 (D), U21.19 (V5)
